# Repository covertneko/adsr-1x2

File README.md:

# ADSR 1x2
This is a dual ADSR eurorack module using most of the available functions of the [Electric Druid ENVGEN8C](https://electricdruid.net/product/envgen8/).

The majority of the schematic is based on examples from the datasheet.

This module also includes an ATmega28P for the very critical purpose of animating the slider shaft leds in time with each envelope stage.

| Specs ||
|---    |---  |
| Size  | 12HP |
| Power | ?mA, +/-12V, 10 pin |
| Depth | 25mm |

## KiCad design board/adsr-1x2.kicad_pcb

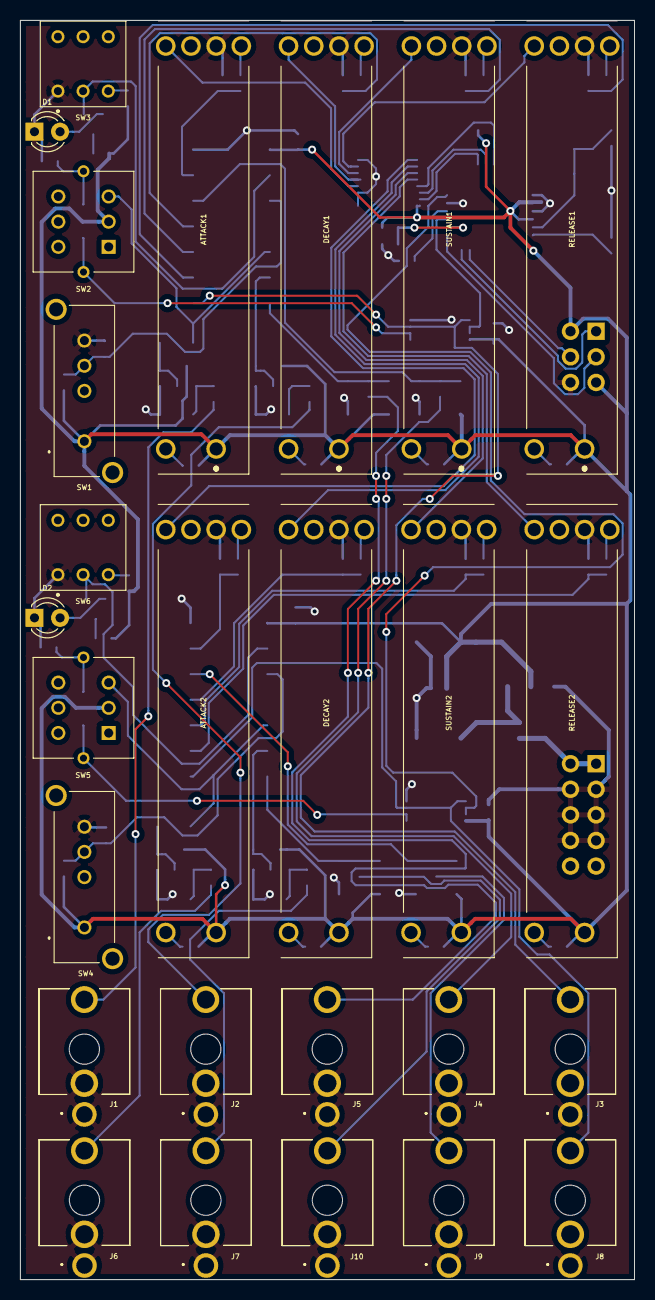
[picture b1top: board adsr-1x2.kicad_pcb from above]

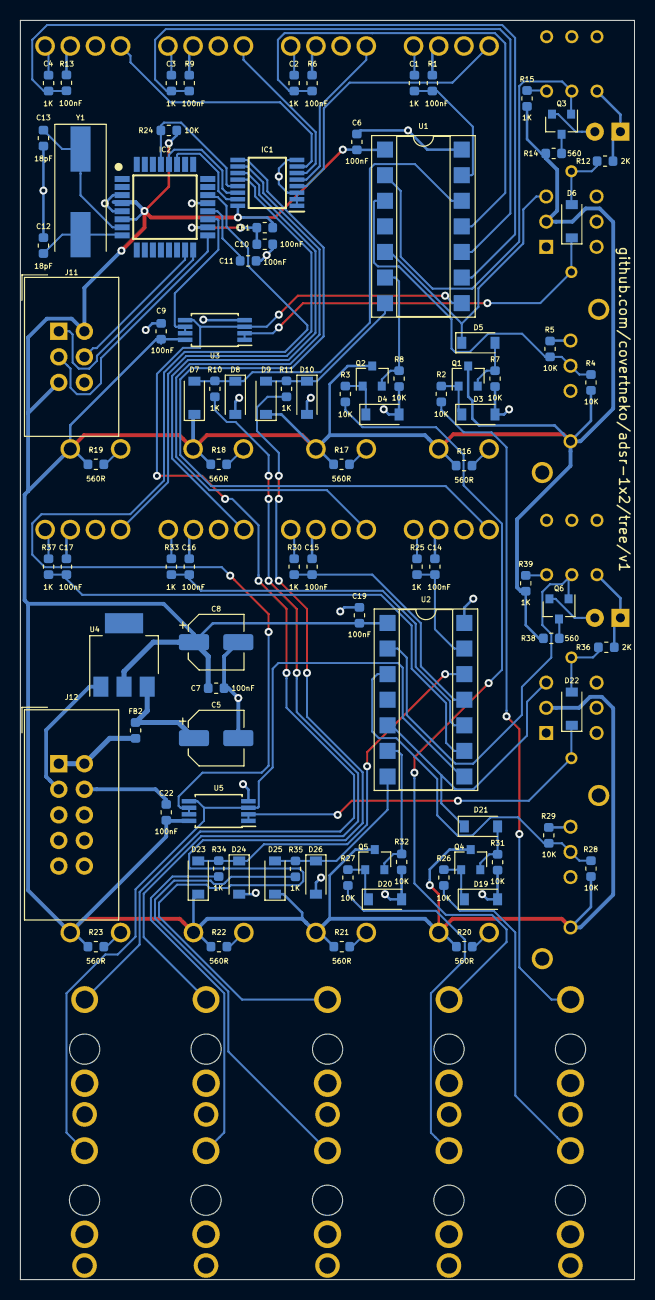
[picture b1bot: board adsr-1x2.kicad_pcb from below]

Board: 2 copper layers, 61.0 x 125.0 mm, 118 parts (92 on the bottom side), 86 nets.

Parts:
ATTACK1, ATTACK2: B10K; PTL3015A1102B1
C1, C2, C3, C4, C6, C7, C9, C10, C11, C14, C15, C16, C17, C19, C22: 100nF; C_0603_1608Metric
C5, C8: 22uF; CP_Elec_5x5.9
C12, C13: 18pF; C_0603_1608Metric
D1, D2: PUNCH; LED_D3.0mm
D3, D4, D5, D6, D19, D20, D21, D22: 1N4148W; D_SOD-123
D7, D8, D9, D10, D23, D24, D25, D26: 1N5819; D_SOD-123
DECAY1, DECAY2: B10K; PTL3015A1102B1
FB1, FB2: FERRITE; L_0603_1608Metric
IC1: TLC59208FIPWR; SOP65P640X120-16N
IC2: ATMEGA328P-AU; QFP80P900X900X120-32N
J1, J6: GATE; PJ301M
J2, J7: RETRIG; PJ301M
J3, J8: ENV; PJ301M
J4, J9: LEVEL; PJ301M
J5, J10: TIME; PJ301M
J11: AVR-ISP-6; IDC-Header_2x03_P2.54mm_Vertical
J12: POWER; IDC-Header_2x05_P2.54mm_Vertical
Q1, Q2, Q3, Q4, Q5, Q6: MMBT3904; SOT-23
R1, R6, R9, R10, R11, R13, R15, R25, R30, R33, R34, R35, R37, R39: 1K; R_0603_1608Metric
R2, R3, R4, R5, R7, R8, R24, R26, R27, R28, R29, R31, R32: 10K; R_0603_1608Metric
R12, R36: 2K; R_0603_1608Metric
R14, R38: 560; R_0603_1608Metric
R16, R17, R18, R19, R20, R21, R22, R23: 560R; R_0603_1608Metric
RELEASE1, RELEASE2: B10K; PTL3015A1102B1
SUSTAIN1, SUSTAIN2: B10K; PTL3015A1102B1
SW1, SW4: MODE; OS103012MU1QP1
SW2, SW5: TRIGGER; LP4EE1PBCTR
SW3, SW6: PUNCH; TL2201EEYA
U1, U2: ENVGEN8C; DIP-14_W7.62mm_SMDSocket_SmallPads
U3, U5: TL072; TSSOP-8_4.4x3mm_P0.65mm
U4: LM1117-5.0; SOT-223
Y1: 20MHz; Crystal_SMD_HC49-SD

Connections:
+5V: ATTACK1.3, ATTACK2.3, C6.1, C7.1, C8.1, C9.2, C19.1, C22.2, D7.1, D9.1, D23.1, D25.1, DECAY1.3, DECAY2.3, FB1.2, IC1.16, IC2.4, IC2.6, J11.2, J11.5, Q1.3, Q2.3, Q4.3, Q5.3, R4.1, R14.2, R15.1, R16.1, R17.1, R18.1, R19.1, R20.1, R21.1, R22.1, R23.1, R24.1, R28.1, R38.2, R39.1, RELEASE1.3, RELEASE2.3, SUSTAIN1.3, SUSTAIN2.3, SW1.1, SW2.2, SW4.1, SW5.2, U1.1, U2.1, U3.8, U4.2, U5.8
+12V: C5.1, FB2.2, U4.3
/ADSR1/ATTACK: C1.1, R1.2, U1.13
/ADSR1/DECAY: C2.1, R6.2, U1.11
/ADSR1/ENV: J3.3, U1.8, U3.3, U3.5
/ADSR1/GATE: D5.1, SW2.3, U1.5
/ADSR1/LEVEL: D7.2, D8.1, R10.1, U1.12
/ADSR1/MODE: R4.2, R5.1, SW1.3, U1.3
/ADSR1/PUNCH: Q3.1, SW3.2, U1.2
/ADSR1/RELEASE: C4.1, R13.2, U1.9
/ADSR1/RETRIG: Q2.2, R8.1, U1.6
/ADSR1/SUSTAIN: C3.1, R9.2, U1.10
/ADSR1/TIME: D9.2, D10.1, R11.1, U1.7
/ADSR2/ATTACK: C14.1, R25.2, U2.13
/ADSR2/DECAY: C15.1, R30.2, U2.11
/ADSR2/ENV: J8.3, U2.8, U5.3, U5.5
/ADSR2/GATE: D21.1, SW5.3, U2.5
/ADSR2/LEVEL: D23.2, D24.1, R34.1, U2.12
/ADSR2/MODE: R28.2, R29.1, SW4.3, U2.3
/ADSR2/PUNCH: Q6.1, SW6.2, U2.2
/ADSR2/RELEASE: C17.1, R37.2, U2.9
/ADSR2/RETRIG: Q5.2, R32.1, U2.6
/ADSR2/SUSTAIN: C16.1, R33.2, U2.10
/ADSR2/TIME: D25.2, D26.1, R35.1, U2.7
/LEDS/ENV1: IC2.19, U3.6, U3.7
/LEDS/ENV2: IC2.22, U5.6, U5.7
/LEDS/LED0: ATTACK1.E1, IC1.4
/LEDS/LED1: DECAY1.E1, IC1.5
/LEDS/LED2: IC1.6, SUSTAIN1.E1
/LEDS/LED3: IC1.7, RELEASE1.E1
/LEDS/LED4: ATTACK2.E1, IC1.9
/LEDS/LED5: DECAY2.E1, IC1.10
/LEDS/LED6: IC1.11, SUSTAIN2.E1
/LEDS/LED7: IC1.12, RELEASE2.E1
/LEDS/MISO: IC2.16, J11.1
/LEDS/MOSI: IC2.15, J11.4
/LEDS/SCK: IC2.17, J11.3
GND: ATTACK1.1, ATTACK2.1, C1.2, C2.2, C3.2, C4.2, C5.2, C6.2, C7.2, C8.2, C9.1, C10.1, C11.1, C12.1, C13.1, C14.2, C15.2, C16.2, C17.2, C19.2, C22.1, D1.1, D2.1, D3.2, D4.2, D8.2, D10.2, D19.2, D20.2, D24.2, D26.2, DECAY1.1, DECAY2.1, IC1.1, IC1.2, IC1.3, IC1.8, IC2.3, IC2.5, IC2.21, J1.1, J1.2, J2.1, J2.2, J3.1, J4.1, J4.2, J5.1, J5.2, J6.1, J6.2, J7.1, J7.2, J8.1, J9.1, J9.2, J10.1, J10.2, J11.6, J12.3, J12.4, J12.5, J12.6, J12.7, J12.8, R5.2, R7.2, R8.2, R12.1, R29.2, R31.2, R32.2, R36.1, RELEASE1.1, RELEASE2.1, SUSTAIN1.1, SUSTAIN2.1, SW1.4, SW3.1, SW4.4, SW6.1, U1.14, U2.14, U3.4, U4.1, U5.4
unnamed: ATTACK1.2, R1.1
unnamed: ATTACK1.B1, R16.2
unnamed: ATTACK2.2, R25.1
unnamed: ATTACK2.B1, R20.2
unnamed: C10.2, FB1.1, IC2.18
unnamed: C11.2, IC2.20
unnamed: C12.2, IC2.8, Y1.2
unnamed: C13.2, IC2.7, Y1.1
unnamed: D1.2, Q3.2
unnamed: D2.2, Q6.2
unnamed: D3.1, Q1.1, R2.2
unnamed: D4.1, Q2.1, R3.2
unnamed: D5.2, Q1.2, R7.1
unnamed: D6.1, SW2.L1, U3.1, U3.2
unnamed: D6.2, R12.2, SW2.L2
unnamed: D19.1, Q4.1, R26.2
unnamed: D20.1, Q5.1, R27.2
unnamed: D21.2, Q4.2, R31.1
unnamed: D22.1, SW5.L1, U5.1, U5.2
unnamed: D22.2, R36.2, SW5.L2
unnamed: DECAY1.2, R6.1
unnamed: DECAY1.B1, R17.2
unnamed: DECAY2.2, R30.1
unnamed: DECAY2.B1, R21.2
unnamed: FB2.1, J12.1, J12.2
unnamed: IC1.13, IC2.29, R24.2
unnamed: IC1.14, IC2.28
unnamed: IC1.15, IC2.27
unnamed: J1.3, R2.1
unnamed: J2.3, R3.1
unnamed: J4.3, R10.2
unnamed: J5.3, R11.2
unnamed: J6.3, R26.1
unnamed: J7.3, R27.1
unnamed: J9.3, R34.2
unnamed: J10.3, R35.2
unnamed: Q3.3, R14.1
unnamed: Q6.3, R38.1
unnamed: R9.1, SUSTAIN1.2
unnamed: R13.1, RELEASE1.2
unnamed: R15.2, SW3.3
unnamed: R18.2, SUSTAIN1.B1
unnamed: R19.2, RELEASE1.B1
unnamed: R22.2, SUSTAIN2.B1
unnamed: R23.2, RELEASE2.B1
unnamed: R33.1, SUSTAIN2.2
unnamed: R37.1, RELEASE2.2
unnamed: R39.2, SW6.3

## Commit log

2020-04-05 Initial commit of first board revision
2020-04-05 Add README
2020-04-06 Fix README formatting
